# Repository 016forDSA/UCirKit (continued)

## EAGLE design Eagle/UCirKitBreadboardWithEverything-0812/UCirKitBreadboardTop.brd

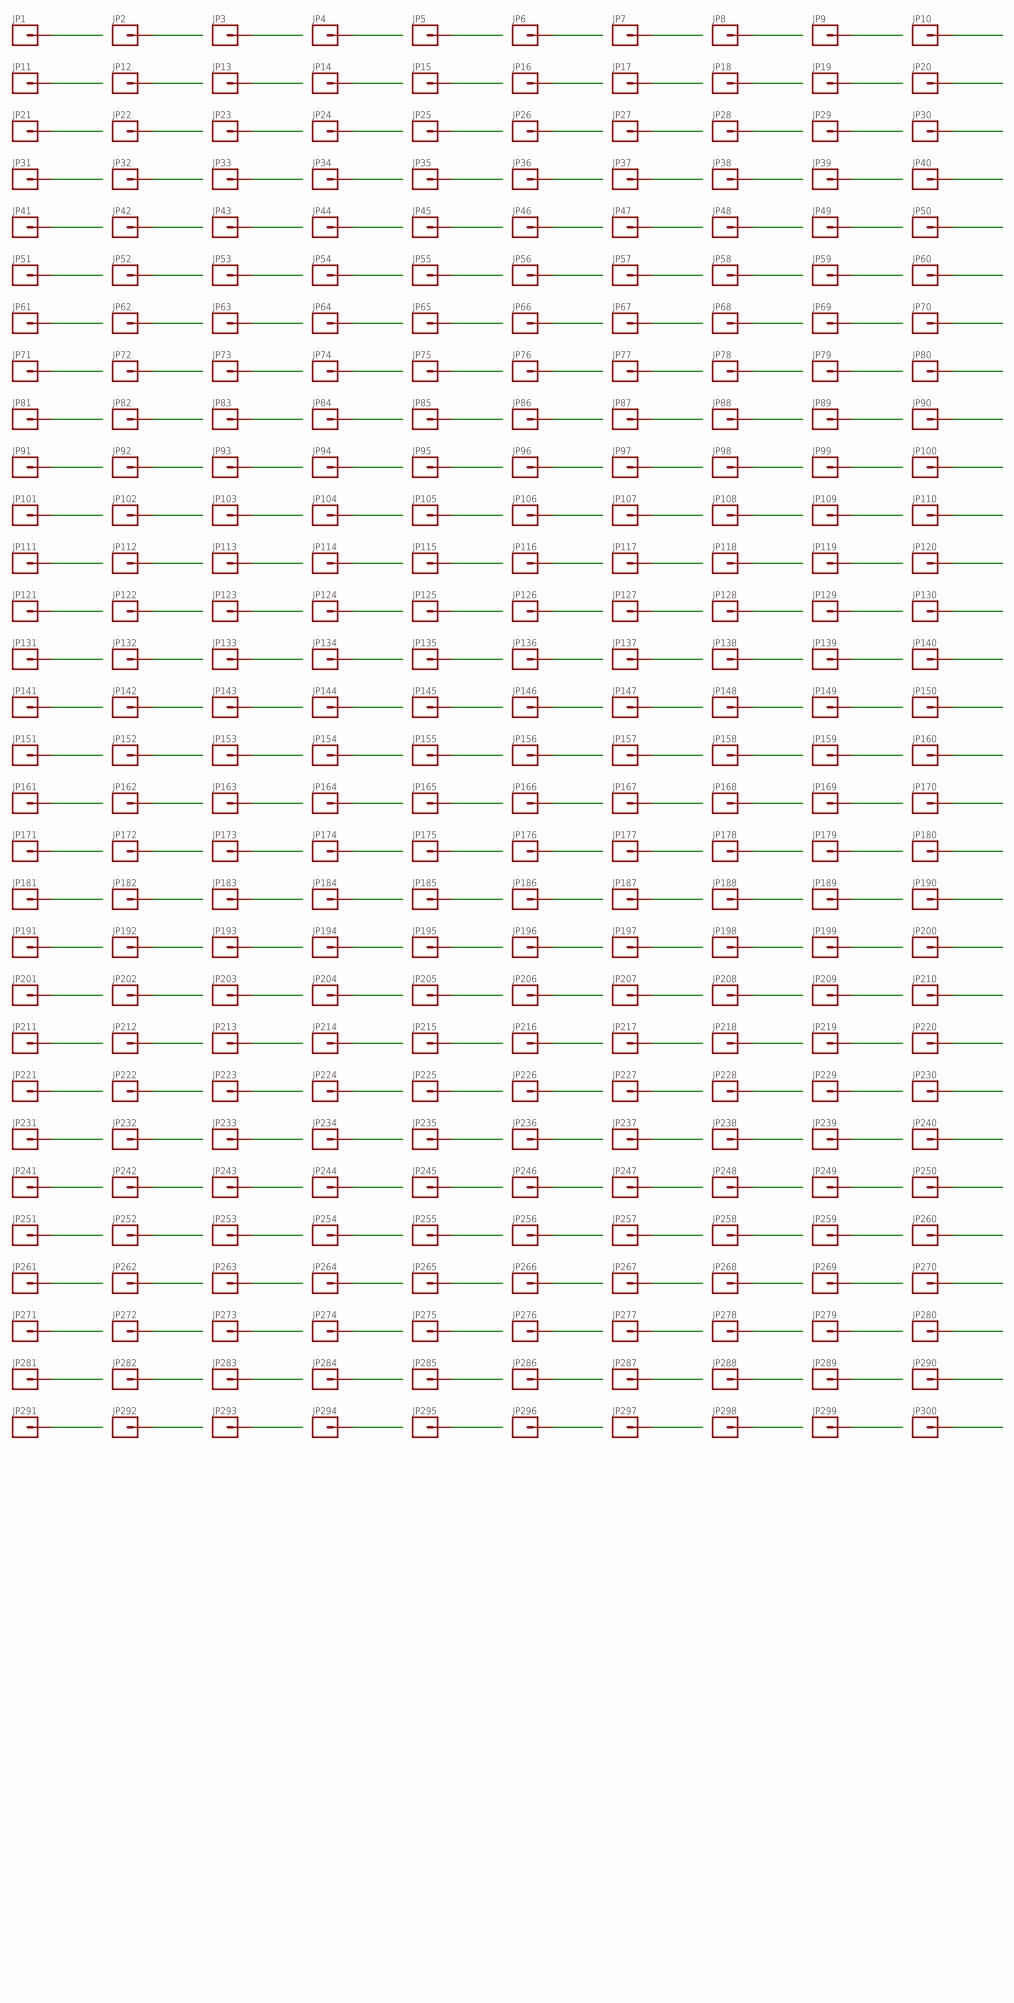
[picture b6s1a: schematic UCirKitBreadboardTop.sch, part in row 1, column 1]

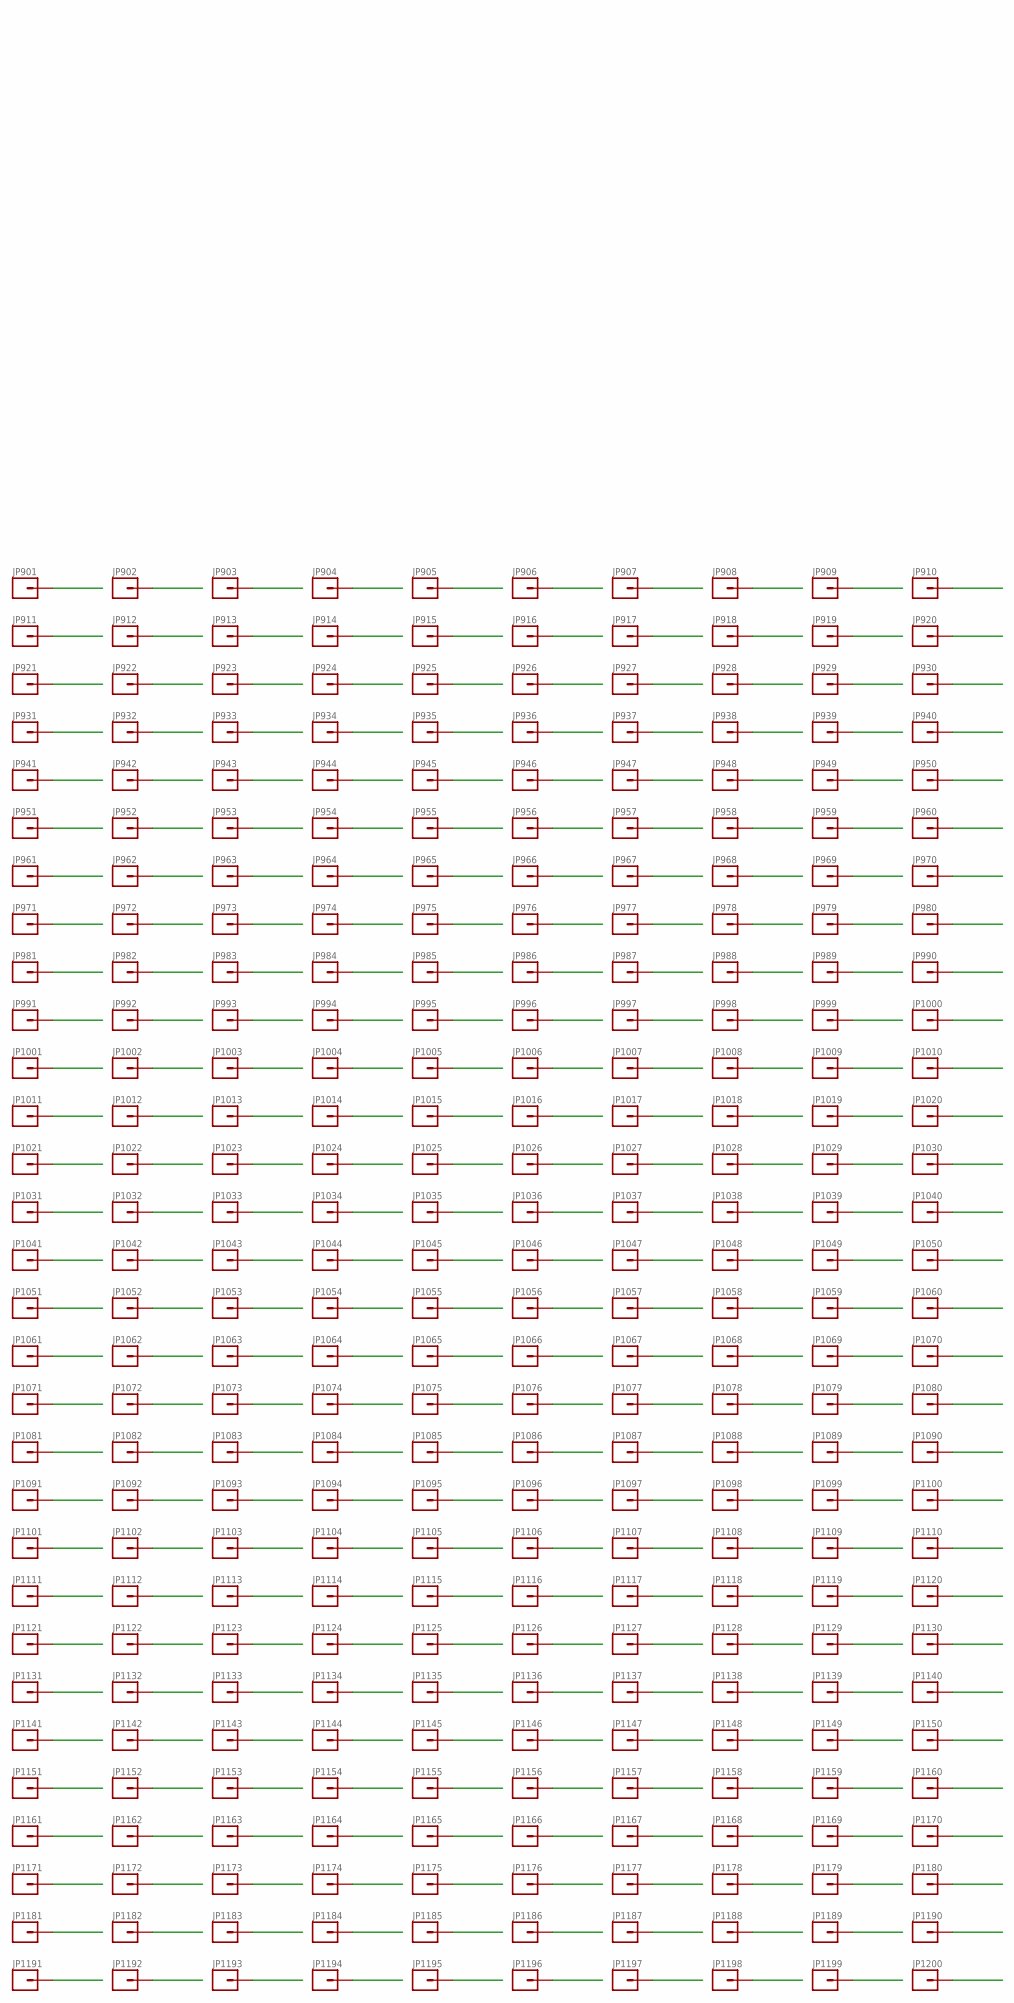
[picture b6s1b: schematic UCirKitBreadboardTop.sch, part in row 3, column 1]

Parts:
JP1, JP2, JP3, JP4, JP5, JP6, JP7, JP8, JP9, JP10, JP11, JP12, JP13, JP14, JP15, JP16, JP17, JP18, JP19, JP20, JP21, JP22, JP23, JP24, JP25, JP26, JP27, JP28, JP29, JP30, JP31, JP32, JP33, JP34, JP35, JP36, JP37, JP38, JP39, JP40, JP41, JP42, JP43, JP44, JP45, JP46, JP47, JP48, JP49, JP50, JP51, JP52, JP53, JP54, JP55, JP56, JP57, JP58, JP59, JP60, JP61, JP62, JP63, JP64, JP65, JP66, JP67, JP68, JP69, JP70, JP71, JP72, JP73, JP74, JP75, JP76, JP77, JP78, JP79, JP80, JP81, JP82, JP83, JP84, JP85, JP86, JP87, JP88, JP89, JP90, JP91, JP92, JP93, JP94, JP95, JP96, JP97, JP98, JP99, JP100, JP101, JP102, JP103, JP104, JP105, JP106, JP107, JP108, JP109, JP110, JP111, JP112, JP113, JP114, JP115, JP116, JP117, JP118, JP119, JP120, JP121, JP122, JP123, JP124, JP125, JP126, JP127, JP128, JP129, JP130, JP131, JP132, JP133, JP134, JP135, JP136, JP137, JP138, JP139, JP140, JP141, JP142, JP143, JP144, JP145, JP146, JP147, JP148, JP149, JP150, JP151, JP152, JP153, JP154, JP155, JP156, JP157, JP158, JP159, JP160, JP161, JP162, JP163, JP164, JP165, JP166, JP167, JP168, JP169, JP170, JP171, JP172, JP173, JP174, JP175, JP176, JP177, JP178, JP179, JP180, JP181, JP182, JP183, JP184, JP185, JP186, JP187, JP188, JP189, JP190, JP191, JP192, JP193, JP194, JP195, JP196, JP197, JP198, JP199, JP200, JP201, JP202, JP203, JP204, JP205, JP206, JP207, JP208, JP209, JP210, JP211, JP212, JP213, JP214, JP215, JP216, JP217, JP218, JP219, JP220, JP221, JP222, JP223, JP224, JP225, JP226, JP227, JP228, JP229, JP230, JP231, JP232, JP233, JP234, JP235, JP236, JP237, JP238, JP239, JP240, JP241, JP242, JP243, JP244, JP245, JP246, JP247, JP248, JP249, JP250, JP251, JP252, JP253, JP254, JP255, JP256, JP257, JP258, JP259, JP260, JP261, JP262, JP263, JP264, JP265, JP266, JP267, JP268, JP269, JP270, JP271, JP272, JP273, JP274, JP275, JP276, JP277, JP278, JP279, JP280, JP281, JP282, JP283, JP284, JP285, JP286, JP287, JP288, JP289, JP290, JP291, JP292, JP293, JP294, JP295, JP296, JP297, JP298, JP299, JP300: M01PTH_WITHOUT_TEXT; 1X01_WITHOUT_TEXT
JP901, JP902, JP903, JP904, JP905, JP906, JP907, JP908, JP909, JP910, JP911, JP912, JP913, JP914, JP915, JP916, JP917, JP918, JP919, JP920, JP921, JP922, JP923, JP924, JP925, JP926, JP927, JP928, JP929, JP930, JP931, JP932, JP933, JP934, JP935, JP936, JP937, JP938, JP939, JP940, JP941, JP942, JP943, JP944, JP945, JP946, JP947, JP948, JP949, JP950, JP951, JP952, JP953, JP954, JP955, JP956, JP957, JP958, JP959, JP960, JP961, JP962, JP963, JP964, JP965, JP966, JP967, JP968, JP969, JP970, JP971, JP972, JP973, JP974, JP975, JP976, JP977, JP978, JP979, JP980, JP981, JP982, JP983, JP984, JP985, JP986, JP987, JP988, JP989, JP990, JP991, JP992, JP993, JP994, JP995, JP996, JP997, JP998, JP999, JP1000, JP1001, JP1002, JP1003, JP1004, JP1005, JP1006, JP1007, JP1008, JP1009, JP1010, JP1011, JP1012, JP1013, JP1014, JP1015, JP1016, JP1017, JP1018, JP1019, JP1020, JP1021, JP1022, JP1023, JP1024, JP1025, JP1026, JP1027, JP1028, JP1029, JP1030, JP1031, JP1032, JP1033, JP1034, JP1035, JP1036, JP1037, JP1038, JP1039, JP1040, JP1041, JP1042, JP1043, JP1044, JP1045, JP1046, JP1047, JP1048, JP1049, JP1050, JP1051, JP1052, JP1053, JP1054, JP1055, JP1056, JP1057, JP1058, JP1059, JP1060, JP1061, JP1062, JP1063, JP1064, JP1065, JP1066, JP1067, JP1068, JP1069, JP1070, JP1071, JP1072, JP1073, JP1074, JP1075, JP1076, JP1077, JP1078, JP1079, JP1080, JP1081, JP1082, JP1083, JP1084, JP1085, JP1086, JP1087, JP1088, JP1089, JP1090, JP1091, JP1092, JP1093, JP1094, JP1095, JP1096, JP1097, JP1098, JP1099, JP1100, JP1101, JP1102, JP1103, JP1104, JP1105, JP1106, JP1107, JP1108, JP1109, JP1110, JP1111, JP1112, JP1113, JP1114, JP1115, JP1116, JP1117, JP1118, JP1119, JP1120, JP1121, JP1122, JP1123, JP1124, JP1125, JP1126, JP1127, JP1128, JP1129, JP1130, JP1131, JP1132, JP1133, JP1134, JP1135, JP1136, JP1137, JP1138, JP1139, JP1140, JP1141, JP1142, JP1143, JP1144, JP1145, JP1146, JP1147, JP1148, JP1149, JP1150, JP1151, JP1152, JP1153, JP1154, JP1155, JP1156, JP1157, JP1158, JP1159, JP1160, JP1161, JP1162, JP1163, JP1164, JP1165, JP1166, JP1167, JP1168, JP1169, JP1170, JP1171, JP1172, JP1173, JP1174, JP1175, JP1176, JP1177, JP1178, JP1179, JP1180, JP1181, JP1182, JP1183, JP1184, JP1185, JP1186, JP1187, JP1188, JP1189, JP1190, JP1191, JP1192, JP1193, JP1194, JP1195, JP1196, JP1197, JP1198, JP1199, JP1200: M01PTH_SMD_1.27X0.635MM_NO_SILK; 1X01_SMD_1.27X0.635MM_NO_SILK

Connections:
0_1439385713: JP1.1, JP961.P$2
0_1439385741: JP2.1, JP1141.P$2
0_1439385772: JP63.1, JP901.P$2
0_1439385798: JP10.1, JP1021.P$2
0_1439385823: JP6.1, JP1161.P$2
0_1439385849: JP68.1, JP1081.P$2
1_1439385713: JP11.1, JP962.P$2
1_1439385741: JP3.1, JP1142.P$2
1_1439385772: JP73.1, JP902.P$2
1_1439385798: JP20.1, JP1022.P$2
1_1439385823: JP7.1, JP1162.P$2
1_1439385849: JP78.1, JP1082.P$2
2_1439385713: JP21.1, JP963.P$2
2_1439385741: JP4.1, JP1143.P$2
2_1439385772: JP64.1, JP903.P$2
2_1439385798: JP30.1, JP1023.P$2
2_1439385823: JP8.1, JP1163.P$2
2_1439385849: JP67.1, JP1083.P$2
3_1439385713: JP31.1, JP964.P$2
3_1439385741: JP5.1, JP1144.P$2
3_1439385772: JP83.1, JP904.P$2
3_1439385798: JP40.1, JP1024.P$2
3_1439385823: JP9.1, JP1164.P$2
3_1439385849: JP88.1, JP1084.P$2
4_1439385713: JP41.1, JP965.P$2
4_1439385741: JP13.1, JP1145.P$2
4_1439385772: JP74.1, JP905.P$2
4_1439385798: JP50.1, JP1025.P$2
4_1439385823: JP18.1, JP1165.P$2
4_1439385849: JP77.1, JP1085.P$2
5_1439385713: JP22.1, JP966.P$2
5_1439385741: JP14.1, JP1146.P$2
5_1439385772: JP65.1, JP906.P$2
5_1439385798: JP29.1, JP1026.P$2
5_1439385823: JP19.1, JP1166.P$2
5_1439385849: JP66.1, JP1086.P$2
6_1439385713: JP51.1, JP967.P$2
6_1439385741: JP15.1, JP1147.P$2
6_1439385772: JP93.1, JP907.P$2
6_1439385798: JP60.1, JP1027.P$2
6_1439385823: JP17.1, JP1167.P$2
6_1439385849: JP98.1, JP1087.P$2
7_1439385713: JP32.1, JP968.P$2
7_1439385741: JP12.1, JP1148.P$2
7_1439385772: JP84.1, JP908.P$2
7_1439385798: JP39.1, JP1028.P$2
7_1439385823: JP16.1, JP1168.P$2
7_1439385849: JP87.1, JP1088.P$2
8_1439385713: JP61.1, JP969.P$2
8_1439385741: JP25.1, JP1149.P$2
8_1439385772: JP75.1, JP909.P$2
8_1439385798: JP70.1, JP1029.P$2
8_1439385823: JP28.1, JP1169.P$2
8_1439385849: JP76.1, JP1089.P$2
9_1439385713: JP42.1, JP970.P$2
9_1439385741: JP24.1, JP1150.P$2
9_1439385772: JP103.1, JP910.P$2
9_1439385798: JP49.1, JP1030.P$2
9_1439385823: JP27.1, JP1170.P$2
9_1439385849: JP108.1, JP1090.P$2
10_1439385713: JP71.1, JP971.P$2
10_1439385741: JP23.1, JP1151.P$2
10_1439385772: JP94.1, JP911.P$2
10_1439385798: JP80.1, JP1031.P$2
10_1439385823: JP26.1, JP1171.P$2
10_1439385849: JP97.1, JP1091.P$2
11_1439385713: JP52.1, JP972.P$2
11_1439385741: JP33.1, JP1152.P$2
11_1439385772: JP113.1, JP912.P$2
11_1439385798: JP59.1, JP1032.P$2
11_1439385823: JP36.1, JP1172.P$2
11_1439385849: JP118.1, JP1092.P$2
12_1439385713: JP81.1, JP973.P$2
12_1439385741: JP34.1, JP1153.P$2
12_1439385772: JP104.1, JP913.P$2
12_1439385798: JP90.1, JP1033.P$2
12_1439385823: JP37.1, JP1173.P$2
12_1439385849: JP107.1, JP1093.P$2
13_1439385713: JP62.1, JP974.P$2
13_1439385741: JP35.1, JP1154.P$2
13_1439385772: JP85.1, JP914.P$2
13_1439385798: JP69.1, JP1034.P$2
13_1439385823: JP38.1, JP1174.P$2
13_1439385849: JP86.1, JP1094.P$2
14_1439385713: JP91.1, JP975.P$2
14_1439385741: JP43.1, JP1155.P$2
14_1439385772: JP123.1, JP915.P$2
14_1439385798: JP100.1, JP1035.P$2
14_1439385823: JP48.1, JP1175.P$2
14_1439385849: JP128.1, JP1095.P$2
15_1439385713: JP72.1, JP976.P$2
15_1439385741: JP44.1, JP1156.P$2
15_1439385772: JP114.1, JP916.P$2
15_1439385798: JP79.1, JP1036.P$2
15_1439385823: JP47.1, JP1176.P$2
15_1439385849: JP117.1, JP1096.P$2
16_1439385713: JP101.1, JP977.P$2
16_1439385741: JP45.1, JP1157.P$2
16_1439385772: JP133.1, JP917.P$2
16_1439385798: JP110.1, JP1037.P$2
16_1439385823: JP46.1, JP1177.P$2
16_1439385849: JP138.1, JP1097.P$2
17_1439385713: JP82.1, JP978.P$2
17_1439385741: JP54.1, JP1158.P$2
17_1439385772: JP124.1, JP918.P$2
17_1439385798: JP89.1, JP1038.P$2
17_1439385823: JP58.1, JP1178.P$2
17_1439385849: JP127.1, JP1098.P$2
18_1439385713: JP111.1, JP979.P$2
18_1439385741: JP55.1, JP1159.P$2
18_1439385772: JP143.1, JP919.P$2
18_1439385798: JP120.1, JP1039.P$2
18_1439385823: JP57.1, JP1179.P$2
18_1439385849: JP96.1, JP1099.P$2
19_1439385713: JP92.1, JP980.P$2
19_1439385741: JP53.1, JP1160.P$2
19_1439385772: JP134.1, JP920.P$2
19_1439385798: JP99.1, JP1040.P$2
19_1439385823: JP56.1, JP1180.P$2
19_1439385849: JP148.1, JP1100.P$2
20_1439385713: JP121.1, JP981.P$2
20_1439385741: JP294.1, JP1181.P$2
20_1439385772: JP153.1, JP921.P$2
20_1439385798: JP130.1, JP1041.P$2
20_1439385823: JP296.1, JP1191.P$2
20_1439385849: JP137.1, JP1101.P$2
21_1439385713: JP102.1, JP982.P$2
21_1439385741: JP284.1, JP1182.P$2
21_1439385772: JP144.1, JP922.P$2
21_1439385798: JP109.1, JP1042.P$2
21_1439385823: JP297.1, JP1192.P$2
21_1439385849: JP158.1, JP1102.P$2
22_1439385713: JP131.1, JP983.P$2
22_1439385741: JP295.1, JP1183.P$2
22_1439385772: JP163.1, JP923.P$2
22_1439385798: JP140.1, JP1043.P$2
22_1439385823: JP287.1, JP1193.P$2
22_1439385849: JP147.1, JP1103.P$2
23_1439385713: JP112.1, JP984.P$2
23_1439385741: JP285.1, JP1184.P$2
23_1439385772: JP154.1, JP924.P$2
23_1439385798: JP119.1, JP1044.P$2
23_1439385823: JP286.1, JP1194.P$2
23_1439385849: JP168.1, JP1104.P$2
24_1439385713: JP141.1, JP985.P$2
24_1439385741: JP273.1, JP1185.P$2
24_1439385772: JP173.1, JP925.P$2
24_1439385798: JP150.1, JP1045.P$2
24_1439385823: JP278.1, JP1195.P$2
24_1439385849: JP157.1, JP1105.P$2
25_1439385713: JP122.1, JP986.P$2
25_1439385741: JP274.1, JP1186.P$2
25_1439385772: JP164.1, JP926.P$2
25_1439385798: JP129.1, JP1046.P$2
25_1439385823: JP277.1, JP1196.P$2
25_1439385849: JP178.1, JP1106.P$2
26_1439385713: JP151.1, JP987.P$2
26_1439385741: JP275.1, JP1187.P$2
26_1439385772: JP183.1, JP927.P$2
26_1439385798: JP160.1, JP1047.P$2
26_1439385823: JP276.1, JP1197.P$2
26_1439385849: JP167.1, JP1107.P$2
27_1439385713: JP132.1, JP988.P$2
27_1439385741: JP264.1, JP1188.P$2
27_1439385772: JP174.1, JP928.P$2
27_1439385798: JP139.1, JP1048.P$2
27_1439385823: JP268.1, JP1198.P$2
27_1439385849: JP188.1, JP1108.P$2
28_1439385713: JP161.1, JP989.P$2
28_1439385741: JP265.1, JP1189.P$2
28_1439385772: JP193.1, JP929.P$2
28_1439385798: JP170.1, JP1049.P$2
28_1439385823: JP267.1, JP1199.P$2
28_1439385849: JP177.1, JP1109.P$2
29_1439385713: JP142.1, JP990.P$2
29_1439385741: JP263.1, JP1190.P$2
29_1439385772: JP184.1, JP930.P$2
29_1439385798: JP149.1, JP1050.P$2
29_1439385823: JP258.1, JP1200.P$2
29_1439385849: JP198.1, JP1110.P$2
30_1439385713: JP171.1, JP991.P$2
30_1439385772: JP203.1, JP931.P$2
30_1439385798: JP180.1, JP1051.P$2
30_1439385849: JP187.1, JP1111.P$2
31_1439385713: JP152.1, JP992.P$2
31_1439385772: JP194.1, JP932.P$2
31_1439385798: JP159.1, JP1052.P$2
31_1439385849: JP208.1, JP1112.P$2
32_1439385713: JP181.1, JP993.P$2
32_1439385772: JP213.1, JP933.P$2
32_1439385798: JP190.1, JP1053.P$2
32_1439385849: JP197.1, JP1113.P$2
33_1439385713: JP162.1, JP994.P$2
33_1439385772: JP204.1, JP934.P$2
33_1439385798: JP169.1, JP1054.P$2
33_1439385849: JP218.1, JP1114.P$2
34_1439385713: JP191.1, JP995.P$2
34_1439385772: JP223.1, JP935.P$2
34_1439385798: JP200.1, JP1055.P$2
34_1439385849: JP207.1, JP1115.P$2
35_1439385713: JP172.1, JP996.P$2
35_1439385772: JP214.1, JP936.P$2
35_1439385798: JP179.1, JP1056.P$2
35_1439385849: JP228.1, JP1116.P$2
36_1439385713: JP201.1, JP997.P$2
36_1439385772: JP233.1, JP937.P$2
36_1439385798: JP210.1, JP1057.P$2
36_1439385849: JP217.1, JP1117.P$2
37_1439385713: JP182.1, JP998.P$2
37_1439385772: JP224.1, JP938.P$2
37_1439385798: JP189.1, JP1058.P$2
37_1439385849: JP238.1, JP1118.P$2
38_1439385713: JP211.1, JP999.P$2
38_1439385772: JP243.1, JP939.P$2
38_1439385798: JP220.1, JP1059.P$2
38_1439385849: JP227.1, JP1119.P$2
39_1439385713: JP192.1, JP1000.P$2
39_1439385772: JP234.1, JP940.P$2
39_1439385798: JP199.1, JP1060.P$2
39_1439385849: JP248.1, JP1120.P$2
40_1439385713: JP221.1, JP1001.P$2
40_1439385772: JP253.1, JP941.P$2
40_1439385798: JP230.1, JP1061.P$2
40_1439385849: JP237.1, JP1121.P$2
41_1439385713: JP202.1, JP1002.P$2
41_1439385772: JP244.1, JP942.P$2
41_1439385798: JP209.1, JP1062.P$2
41_1439385849: JP247.1, JP1122.P$2
42_1439385713: JP231.1, JP1003.P$2
42_1439385772: JP215.1, JP943.P$2
42_1439385798: JP240.1, JP1063.P$2
42_1439385849: JP216.1, JP1123.P$2
43_1439385713: JP212.1, JP1004.P$2
43_1439385772: JP254.1, JP944.P$2
43_1439385798: JP219.1, JP1064.P$2
43_1439385849: JP257.1, JP1124.P$2
44_1439385713: JP241.1, JP1005.P$2
44_1439385772: JP225.1, JP945.P$2
44_1439385798: JP250.1, JP1065.P$2
44_1439385849: JP226.1, JP1125.P$2
45_1439385713: JP222.1, JP1006.P$2
45_1439385772: JP235.1, JP946.P$2
45_1439385798: JP229.1, JP1066.P$2
45_1439385849: JP236.1, JP1126.P$2
46_1439385713: JP251.1, JP1007.P$2
46_1439385772: JP245.1, JP947.P$2
46_1439385798: JP260.1, JP1067.P$2
46_1439385849: JP246.1, JP1127.P$2
47_1439385713: JP232.1, JP1008.P$2
47_1439385772: JP255.1, JP948.P$2
47_1439385798: JP239.1, JP1068.P$2
47_1439385849: JP256.1, JP1128.P$2
48_1439385713: JP261.1, JP1009.P$2
48_1439385772: JP205.1, JP949.P$2
48_1439385798: JP270.1, JP1069.P$2
48_1439385849: JP266.1, JP1129.P$2
49_1439385713: JP242.1, JP1010.P$2
49_1439385772: JP195.1, JP950.P$2
49_1439385798: JP249.1, JP1070.P$2
49_1439385849: JP206.1, JP1130.P$2
50_1439385713: JP271.1, JP1011.P$2
50_1439385772: JP185.1, JP951.P$2
50_1439385798: JP280.1, JP1071.P$2
50_1439385849: JP196.1, JP1131.P$2
51_1439385713: JP252.1, JP1012.P$2
51_1439385772: JP175.1, JP952.P$2
51_1439385798: JP259.1, JP1072.P$2
51_1439385849: JP186.1, JP1132.P$2
52_1439385713: JP281.1, JP1013.P$2
52_1439385772: JP165.1, JP953.P$2
52_1439385798: JP290.1, JP1073.P$2
52_1439385849: JP176.1, JP1133.P$2
53_1439385713: JP262.1, JP1014.P$2
53_1439385772: JP155.1, JP954.P$2
53_1439385798: JP269.1, JP1074.P$2
53_1439385849: JP166.1, JP1134.P$2
54_1439385713: JP291.1, JP1015.P$2
54_1439385772: JP145.1, JP955.P$2
54_1439385798: JP300.1, JP1075.P$2
54_1439385849: JP156.1, JP1135.P$2
55_1439385713: JP272.1, JP1016.P$2
55_1439385772: JP135.1, JP956.P$2
55_1439385798: JP279.1, JP1076.P$2
55_1439385849: JP146.1, JP1136.P$2
56_1439385713: JP282.1, JP1017.P$2
56_1439385772: JP125.1, JP957.P$2
56_1439385798: JP289.1, JP1077.P$2
56_1439385849: JP136.1, JP1137.P$2
57_1439385713: JP292.1, JP1018.P$2
57_1439385772: JP115.1, JP958.P$2
57_1439385798: JP299.1, JP1078.P$2
57_1439385849: JP126.1, JP1138.P$2
58_1439385713: JP293.1, JP1019.P$2
58_1439385772: JP105.1, JP959.P$2
58_1439385798: JP298.1, JP1079.P$2
58_1439385849: JP116.1, JP1139.P$2
59_1439385713: JP283.1, JP1020.P$2
59_1439385772: JP95.1, JP960.P$2
59_1439385798: JP288.1, JP1080.P$2
59_1439385849: JP106.1, JP1140.P$2

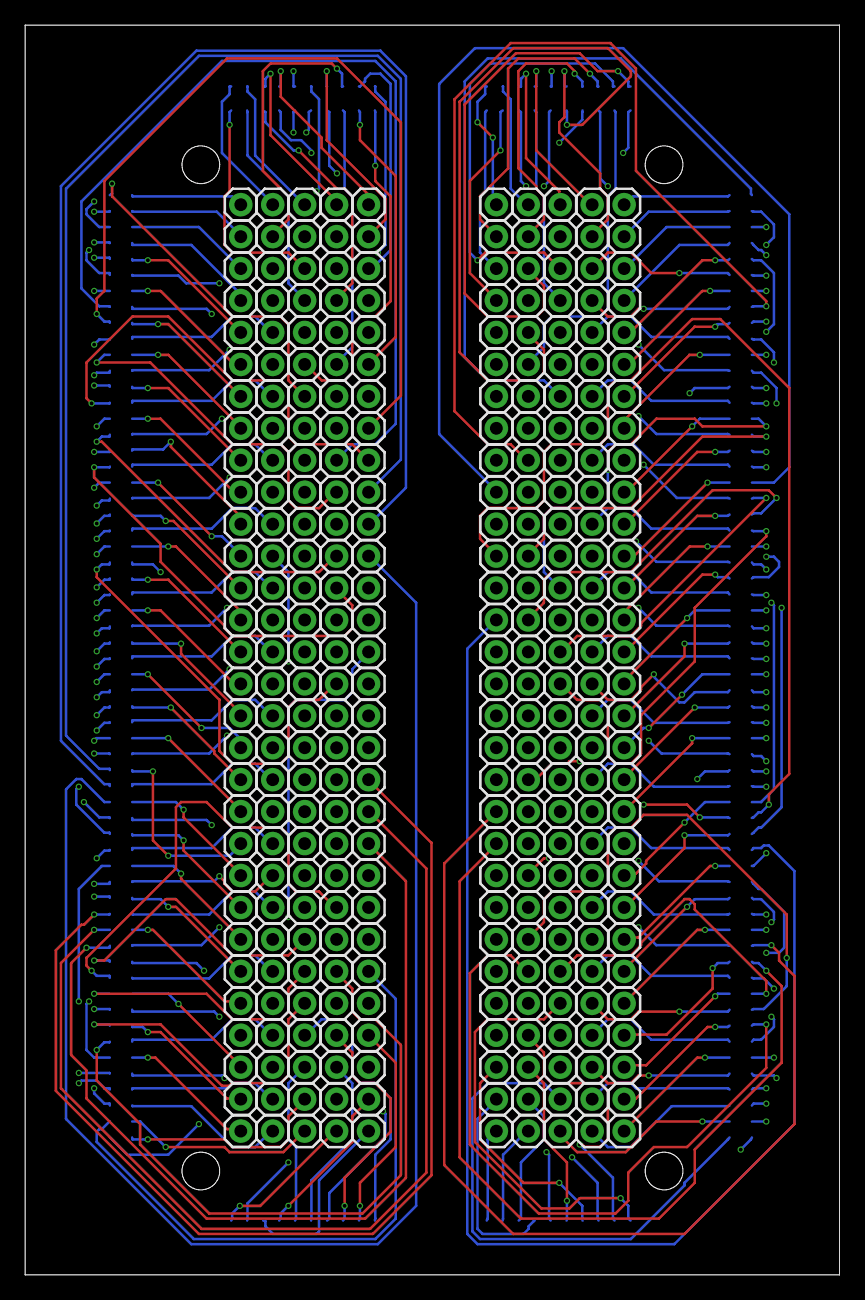
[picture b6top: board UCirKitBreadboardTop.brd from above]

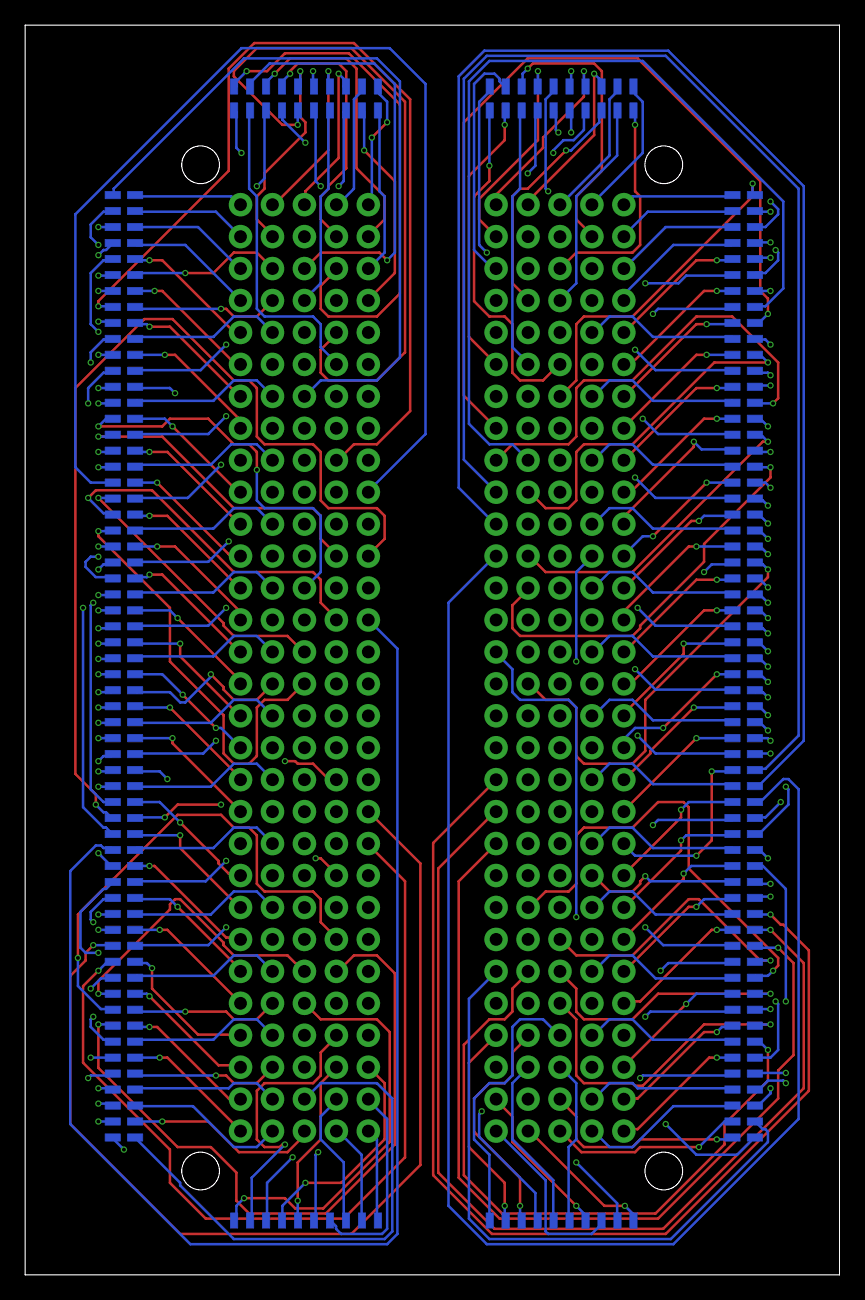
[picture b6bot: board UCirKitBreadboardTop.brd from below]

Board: 4 copper layers, 64.8 x 99.4 mm, 600 parts (300 on the bottom side), 300 nets.
